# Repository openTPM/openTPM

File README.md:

# openTPM
open hardware security device

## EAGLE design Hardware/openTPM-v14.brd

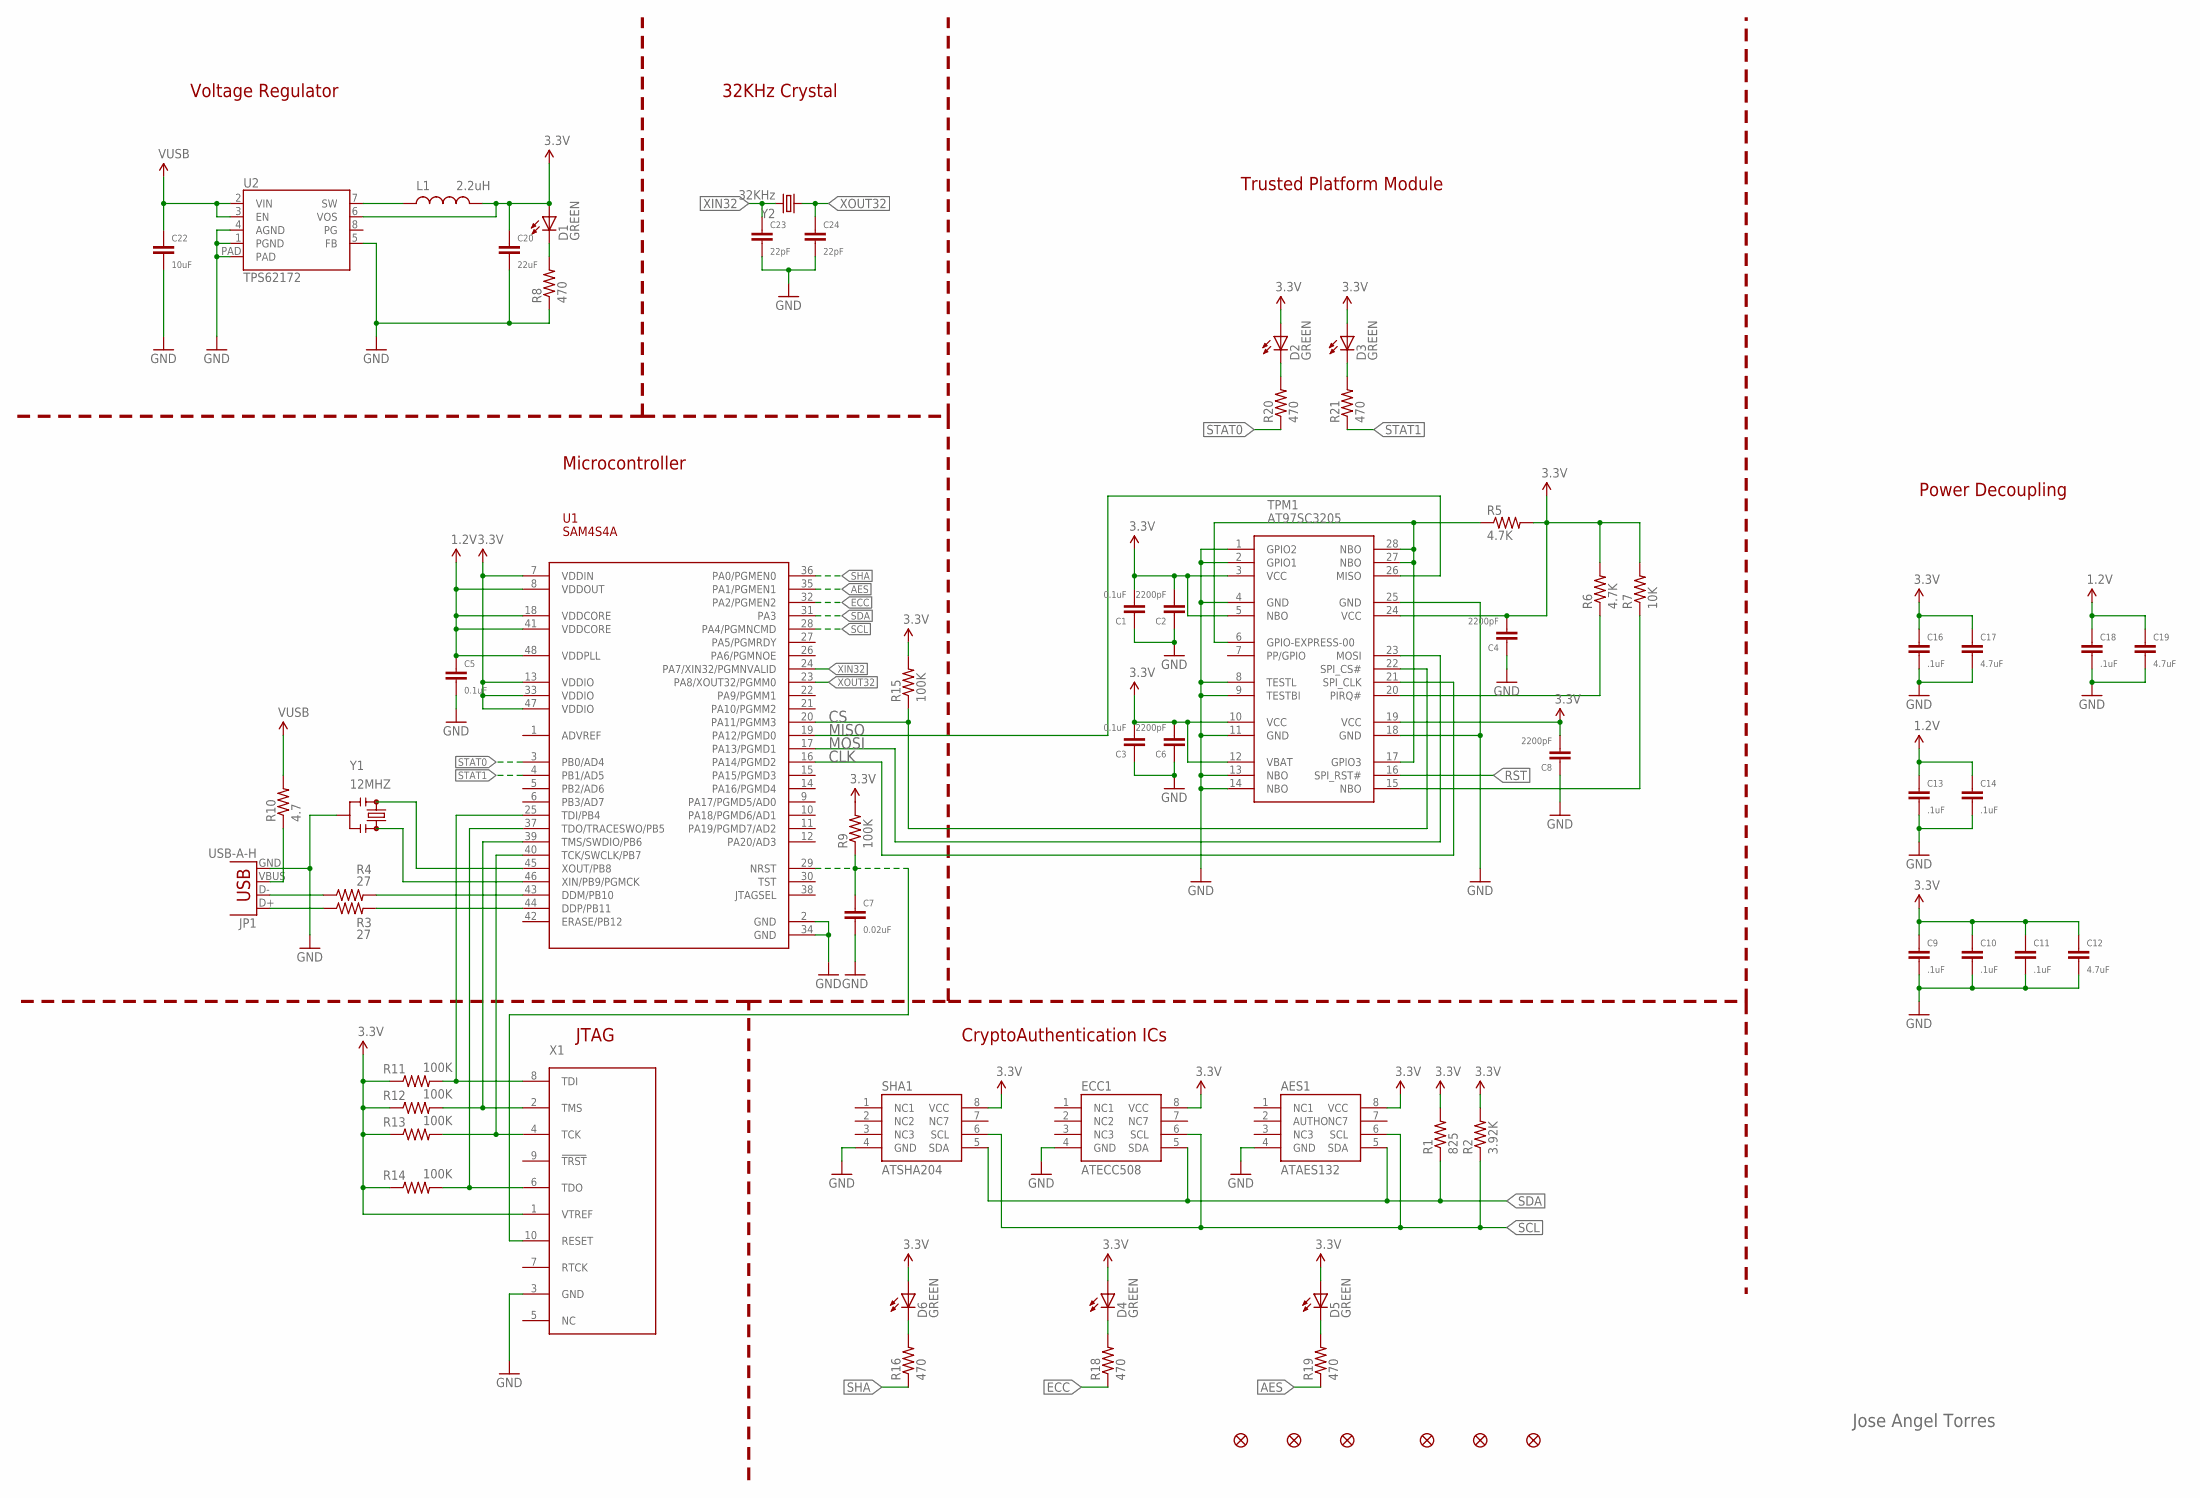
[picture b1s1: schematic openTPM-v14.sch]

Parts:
AES1: ATAES132; CRYPTOTRONIX_SOIC8
C1, C3, C5: 0.1uF; 0402
C2, C4, C6, C8: 2200pF; 0402
C7: 0.02uF; 0402
C9, C10, C11, C13, C14, C16, C18: .1uF; 0402
C12, C17, C19: 4.7uF; 0402
C20: 22uF; 0603
C22: 10uF; 0402
C23, C24: 22pF; 0402
D1, D2, D3, D4, D5, D6: GREEN; SPARKFUN-LED_LED-0603
ECC1: ATECC508; CRYPTOTRONIX_SOIC8
FID1, FID2, FID3, FID4, FID5, FID6: SPARKFUN-AESTHETICS_FIDUCIAL1X2; SPARKFUN-AESTHETICS_FIDUCIAL-1X2
JP1: USB-A-H
L1: 2.2uH; C0402
R1: 825; 0402
R2: 3.92K; 0402
R3, R4: 27; 0402
R5, R6: 4.7K; 0402
R7: 10K; 0402
R8, R16, R18, R19, R20, R21: 470; 0402
R9, R11, R12, R13, R14, R15: 100K; 0402
R10: 4.7; 0402
SHA1: ATSHA204; CRYPTOTRONIX_SOIC8
TPM1: AT97SC3205; TSSOP28
U1: SAM4S4A; LQFP-48
U2: TPS62172; WSON-8-PAD
X1: TC2050-NL-MCP-NL; TC2030-MCP-NL
Y1: 12MHZ; RESONATOR-SMD
Y2: 32KHz; CRYSTAL-32KHZ-SMD_EPSON_MC146

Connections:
1.2V: C5.1, C13.1, C14.1, C18.1, C19.1, U1.8 (VDDOUT), U1.18 (VDDCORE), U1.41 (VDDCORE), U1.48 (VDDPLL)
3.3V: AES1.8 (VCC), C1.2, C2.2, C3.2, C4.2, C6.2, C8.2, C9.1, C10.1, C11.1, C12.1, C16.1, C17.1, C20.1, D1.A, D2.A, D3.A, D4.A, D5.A, D6.A, ECC1.8 (VCC), L1.2, R1.2, R2.2, R5.2, R6.2, R7.2, R9.2, R11.1, R12.1, R13.1, R14.1, R15.2, SHA1.8 (VCC), TPM1.3 (VCC), TPM1.5 (NBO), TPM1.10 (VCC), TPM1.12 (VBAT), TPM1.19 (VCC), TPM1.24 (VCC), U1.7 (VDDIN), U1.13 (VDDIO), U1.33 (VDDIO), U1.47 (VDDIO), U2.6 (VOS), X1.1 (VTREF)
AES: R19.1, U1.35 (PA1/PGMEN1)
CLK: TPM1.21 (SPI_CLK), U1.16 (PA14/PGMD2)
CS: R15.1, TPM1.22 (SPI_CS#), U1.20 (PA11/PGMM3)
ECC: R18.1, U1.32 (PA2/PGMEN2)
GND: AES1.4 (GND), C1.1, C2.1, C3.1, C4.1, C5.2, C6.1, C7.2, C8.1, C9.2, C10.2, C11.2, C12.2, C13.2, C14.2, C16.2, C17.2, C18.2, C19.2, C20.2, C22.2, C23.2, C24.2, ECC1.4 (GND), JP1.GND, R8.1, SHA1.4 (GND), TPM1.1 (GPIO2), TPM1.2 (GPIO1), TPM1.4 (GND), TPM1.8 (TESTL), TPM1.9 (TESTBI), TPM1.11 (GND), TPM1.13 (NBO), TPM1.14 (NBO), TPM1.18 (GND), TPM1.25 (GND), U1.2 (GND), U1.34 (GND), U2.1 (PGND), U2.4 (AGND), U2.5 (FB), U2.PAD, X1.3 (GND), Y1.2
MISO: TPM1.26 (MISO), U1.19 (PA12/PGMD0)
MOSI: TPM1.23 (MOSI), U1.17 (PA13/PGMD1)
unnamed: R4.2, U1.43 (DDM/PB10)
unnamed: R3.2, U1.44 (DDP/PB11)
unnamed: R11.2, U1.25 (TDI/PB4), X1.8 (TDI)
unnamed: R14.2, U1.37 (TDO/TRACESWO/PB5), X1.6 (TDO)
unnamed: R12.2, U1.39 (TMS/SWDIO/PB6), X1.2 (TMS)
unnamed: R13.2, U1.40 (TCK/SWCLK/PB7), X1.4 (TCK)
unnamed: U1.45 (XOUT/PB8), Y1.1
unnamed: U1.46 (XIN/PB9/PGMCK), Y1.3
unnamed: R6.1, TPM1.20 (PIRQ#)
unnamed: JP1.D-, R4.1
unnamed: JP1.D+, R3.1
unnamed: JP1.VBUS, R10.1
unnamed: R7.1, TPM1.15 (NBO)
unnamed: R5.1, TPM1.6 (GPIO-EXPRESS-00), TPM1.17 (GPIO3), TPM1.27 (NBO), TPM1.28 (NBO)
unnamed: D4.C, R18.2
unnamed: L1.1, U2.7 (SW)
unnamed: D1.C, R8.2
unnamed: D6.C, R16.2
unnamed: D5.C, R19.2
unnamed: D2.C, R20.2
unnamed: D3.C, R21.2
RST: C7.1, R9.1, TPM1.16 (SPI_RST#), U1.29 (NRST), X1.10 (RESET)
SCL: AES1.6 (SCL), ECC1.6 (SCL), R2.1, SHA1.6 (SCL), U1.28 (PA4/PGMNCMD)
SDA: AES1.5 (SDA), ECC1.5 (SDA), R1.1, SHA1.5 (SDA), U1.31 (PA3)
SHA: R16.1, U1.36 (PA0/PGMEN0)
STAT0: R20.1, U1.3 (PB0/AD4)
STAT1: R21.1, U1.4 (PB1/AD5)
VUSB: C22.1, R10.2, U2.2 (VIN), U2.3 (EN)
XIN32: C23.1, U1.24 (PA7/XIN32/PGMNVALID), Y2.P$1 (2)
XOUT32: C24.1, U1.23 (PA8/XOUT32/PGMM0), Y2.P$2 (1)

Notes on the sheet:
Jose Angel Torres
32KHz Crystal
Voltage Regulator
Microcontroller
Trusted Platform Module
CryptoAuthentication ICs
JTAG
Power Decoupling

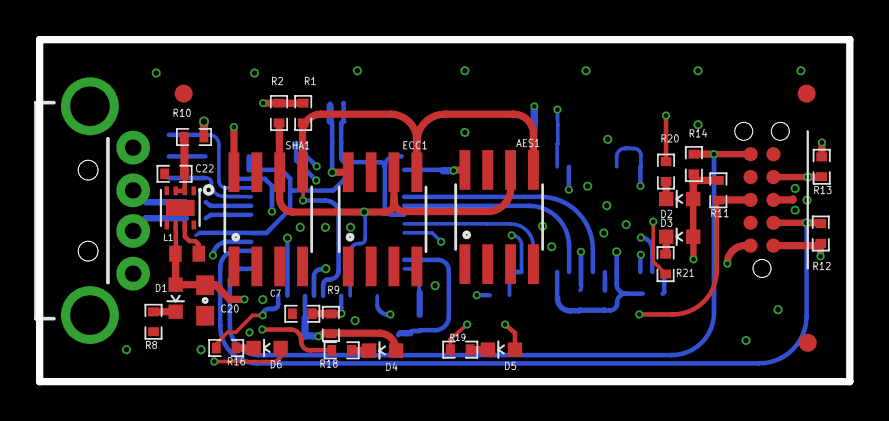
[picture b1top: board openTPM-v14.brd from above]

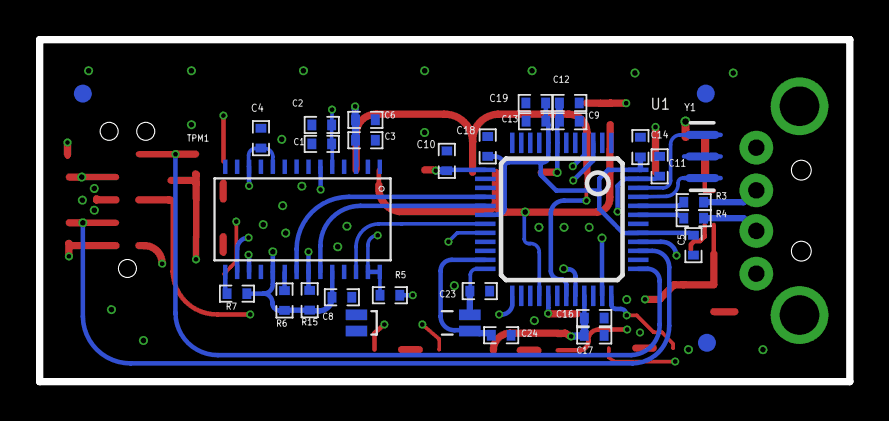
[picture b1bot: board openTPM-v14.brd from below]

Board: 4 copper layers, 45.0 x 19.0 mm, 65 parts (32 on the bottom side), 39 nets.

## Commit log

2015-07-21 schematic complete, board has 57 airwires
2015-07-29 initial github commit
2015-07-29 git ignore file
2015-07-29 Reorg of Hardware folder
2015-07-30 Render of openTPM
2015-07-30 Render of openTPM (part 2)
2015-07-30 reorg of images, update to board trace widths for power, added to gitignore
2015-07-30 update ignore, add circuithub files
2015-07-30 finalizing gitignore
2017-04-01 producing PVT version
2017-04-15 add v3.0
2017-04-16 ignore and CAM
2017-04-16 cleanup and gerbers
2017-04-16 ignore user files and cleanup moved files
2017-04-20 finished routing PCB, placed LED's, added Test points, cleaned up power routing, as well as created working gerbers. -Scott@electricmonkies.com.
2017-05-07 version 3.5 with unrouted spi flash
2017-05-09 cleaned silk up, added logo and binary words.
2018-01-16 OpenTPM v37 upload routing done

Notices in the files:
parts and their libraries:
TPM: ©2009 ROFA.cz
TPM: Released under the Creative Commons
TPM: http://creativecommons.org/licenses/by-sa/3.0
